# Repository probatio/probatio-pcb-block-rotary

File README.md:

# probatio-pcb-block-rotary
pcb for a probatio block of a rotary encoder with LEDs

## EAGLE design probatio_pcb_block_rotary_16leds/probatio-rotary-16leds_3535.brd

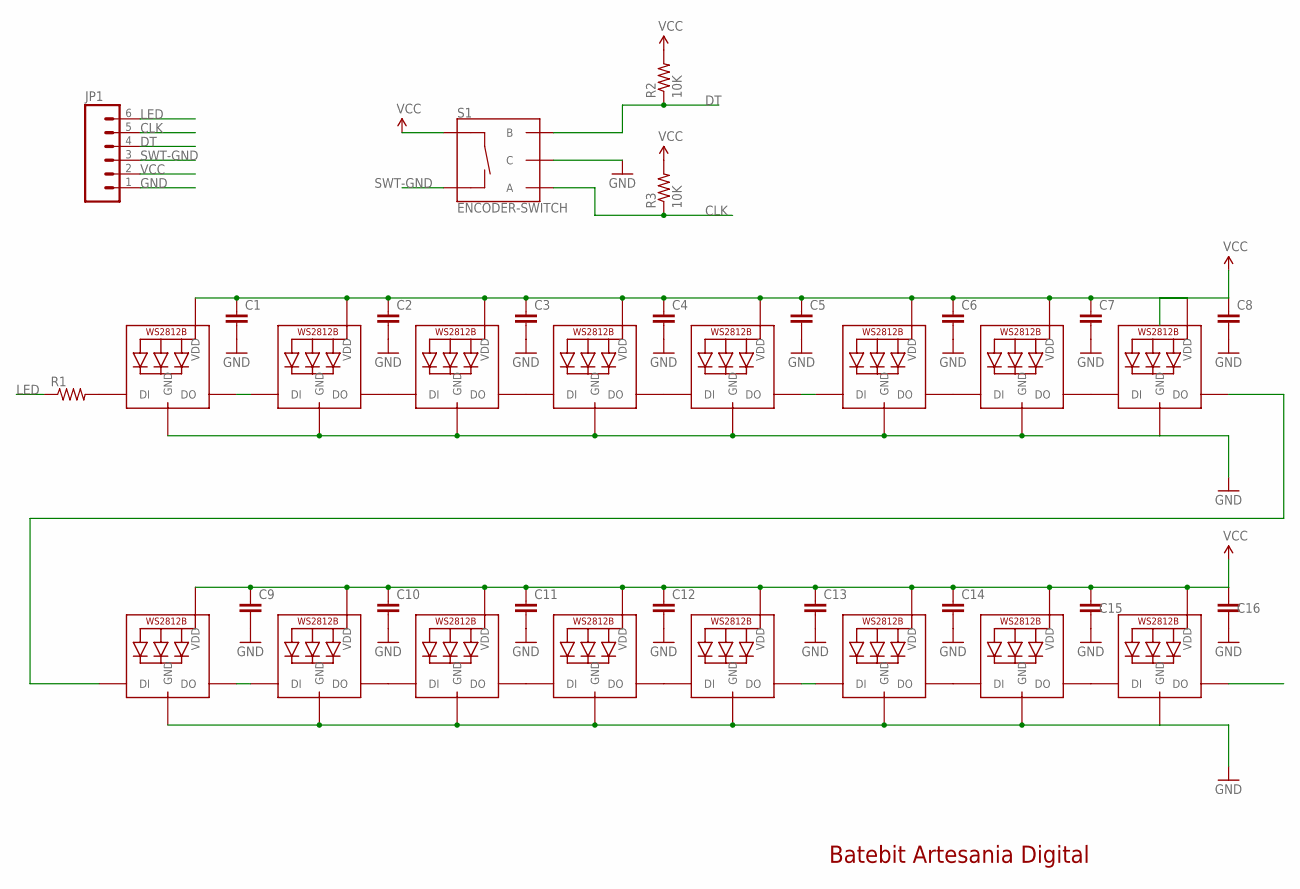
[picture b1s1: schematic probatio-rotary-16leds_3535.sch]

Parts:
C1, C2, C3, C4, C5, C6, C7, C8, C9, C10, C11, C12, C13, C14, C15, C16: CAP0805-CAP; 0805-CAP
JP1: M06SILK_FEMALE_PTH; 1X06
LED1, LED2, LED3, LED4, LED5, LED6, LED7, LED8, LED9, LED10, LED11, LED12, LED13, LED14, LED15, LED16: WS2812B3535; LED3535
R1: RESISTOR0805-RES; 0805-RES
R2, R3: 10K; 0805-RES
S1: ENCODER-SWITCH; ROTARY_ENC_PLAIN

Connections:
CLK: JP1.5, R3.1, S1.A
DT: JP1.4, R2.1, S1.B
GND: C1.2, C2.2, C3.2, C4.2, C5.2, C6.2, C7.2, C8.2, C9.2, C10.2, C11.2, C12.2, C13.2, C14.2, C15.2, C16.2, JP1.1, LED1.4 (GND), LED2.4 (GND), LED3.4 (GND), LED4.4 (GND), LED5.4 (GND), LED6.4 (GND), LED7.4 (GND), LED8.4 (GND), LED9.4 (GND), LED10.4 (GND), LED11.4 (GND), LED12.4 (GND), LED13.4 (GND), LED14.4 (GND), LED15.4 (GND), LED16.4 (GND), S1.C
LED: JP1.6, R1.1
unnamed: LED1.3 (DO), LED2.1 (DI)
unnamed: LED2.3 (DO), LED3.1 (DI)
unnamed: LED3.3 (DO), LED4.1 (DI)
unnamed: LED5.3 (DO), LED6.1 (DI)
unnamed: LED6.3 (DO), LED7.1 (DI)
unnamed: LED7.3 (DO), LED8.1 (DI)
unnamed: LED4.3 (DO), LED5.1 (DI)
unnamed: LED9.3 (DO), LED10.1 (DI)
unnamed: LED10.3 (DO), LED11.1 (DI)
unnamed: LED11.3 (DO), LED12.1 (DI)
unnamed: LED13.3 (DO), LED14.1 (DI)
unnamed: LED14.3 (DO), LED15.1 (DI)
unnamed: LED15.3 (DO), LED16.1 (DI)
unnamed: LED12.3 (DO), LED13.1 (DI)
unnamed: LED8.3 (DO), LED9.1 (DI)
unnamed: LED1.1 (DI), R1.2
SWT-GND: JP1.3, S1.SW-
VCC: C1.1, C2.1, C3.1, C4.1, C5.1, C6.1, C7.1, C8.1, C9.1, C10.1, C11.1, C12.1, C13.1, C14.1, C15.1, C16.1, JP1.2, LED1.2 (VDD), LED2.2 (VDD), LED3.2 (VDD), LED4.2 (VDD), LED5.2 (VDD), LED6.2 (VDD), LED7.2 (VDD), LED8.2 (VDD), LED9.2 (VDD), LED10.2 (VDD), LED11.2 (VDD), LED12.2 (VDD), LED13.2 (VDD), LED14.2 (VDD), LED15.2 (VDD), LED16.2 (VDD), R2.2, R3.2, S1.SW+

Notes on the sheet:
Batebit Artesania Digital

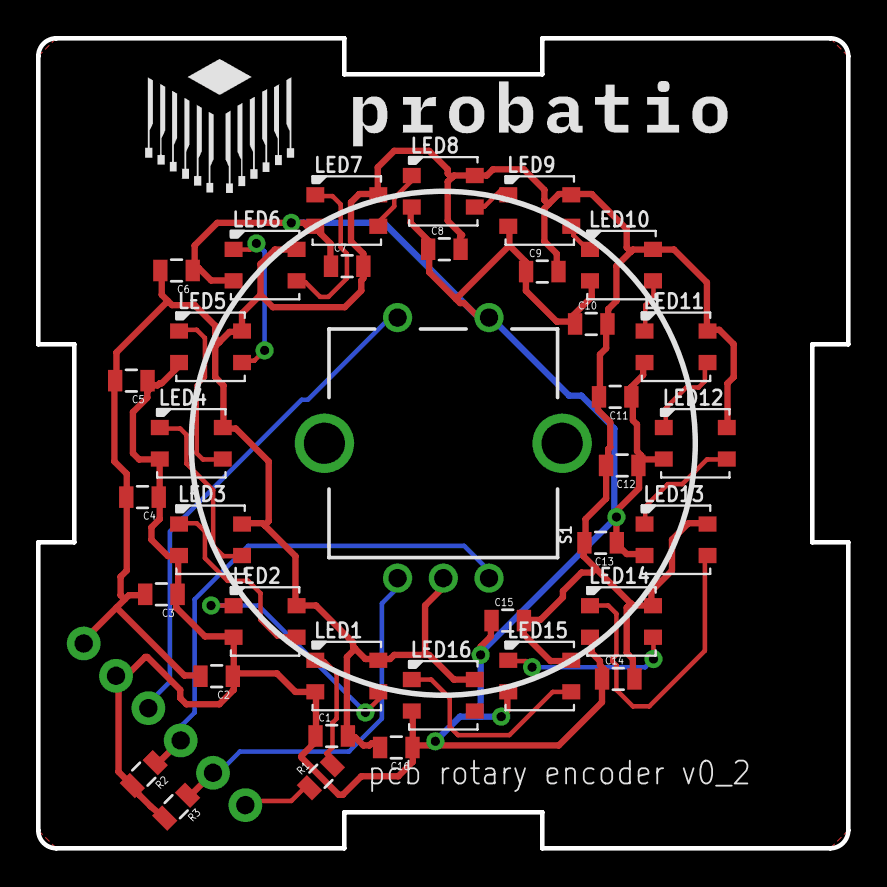
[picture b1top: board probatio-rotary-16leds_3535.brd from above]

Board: 2 copper layers, 45.0 x 45.0 mm, 38 parts (1 on the bottom side), 22 nets.

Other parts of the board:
U$3: PROBATIO

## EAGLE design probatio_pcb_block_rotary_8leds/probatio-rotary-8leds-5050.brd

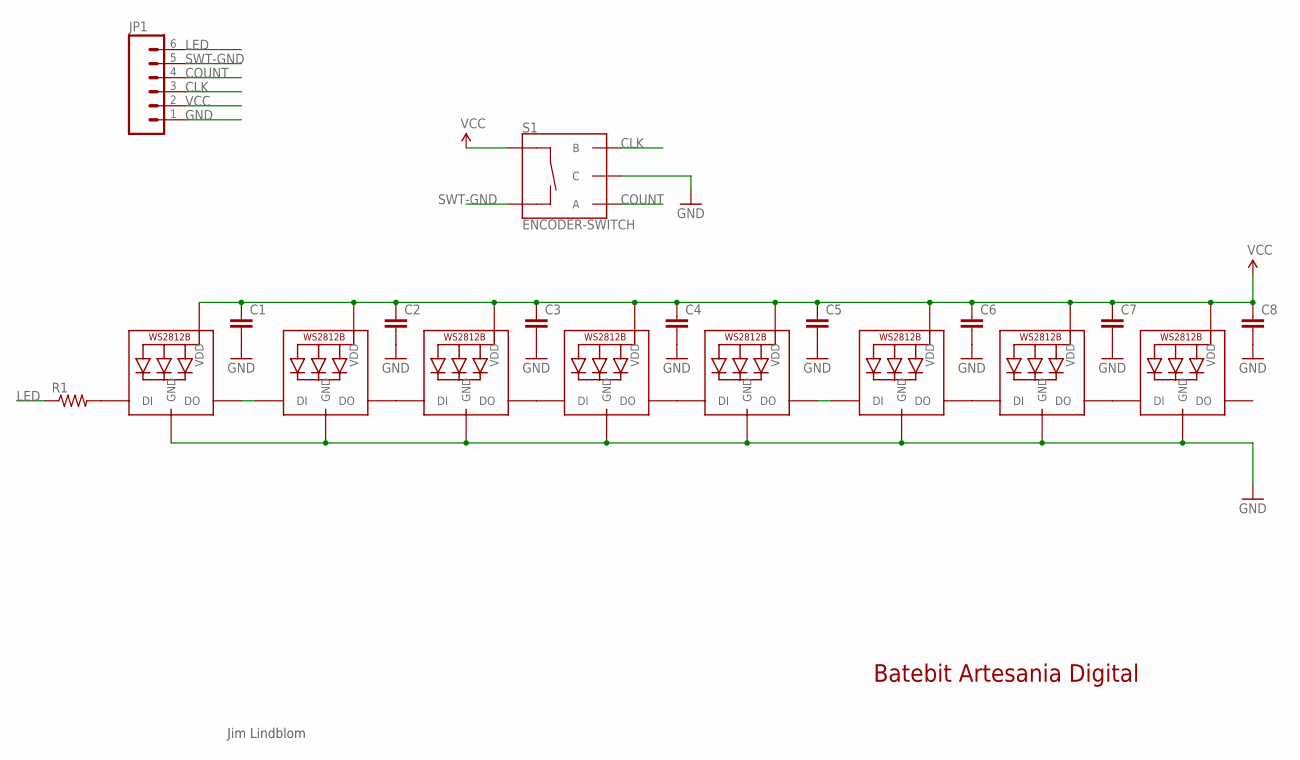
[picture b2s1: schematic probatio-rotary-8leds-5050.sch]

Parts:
C1, C2, C3, C4, C5, C6, C7, C8: CAP0805-CAP; 0805-CAP
JP1: M06SILK_FEMALE_PTH; 1X06
LED1, LED2, LED3, LED4, LED5, LED6, LED7, LED8: WS2812B5050; WS2812B
R1: RESISTOR0805-RES; 0805-RES
S1: ENCODER-SWITCH; ROTARY_ENC_PLAIN

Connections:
CLK: JP1.3, S1.B
COUNT: JP1.4, S1.A
GND: C1.2, C2.2, C3.2, C4.2, C5.2, C6.2, C7.2, C8.2, JP1.1, LED1.3-GND (GND), LED2.3-GND (GND), LED3.3-GND (GND), LED4.3-GND (GND), LED5.3-GND (GND), LED6.3-GND (GND), LED7.3-GND (GND), LED8.3-GND (GND), S1.C
LED: JP1.6, R1.1
unnamed: LED1.2-DOUT (DO), LED2.4-DIN (DI)
unnamed: LED1.4-DIN (DI), R1.2
unnamed: LED2.2-DOUT (DO), LED3.4-DIN (DI)
unnamed: LED5.2-DOUT (DO), LED6.4-DIN (DI)
unnamed: LED3.2-DOUT (DO), LED4.4-DIN (DI)
unnamed: LED4.2-DOUT (DO), LED5.4-DIN (DI)
unnamed: LED6.2-DOUT (DO), LED7.4-DIN (DI)
unnamed: LED7.2-DOUT (DO), LED8.4-DIN (DI)
SWT-GND: JP1.5, S1.SW-
VCC: C1.1, C2.1, C3.1, C4.1, C5.1, C6.1, C7.1, C8.1, JP1.2, LED1.1-VDD (VDD), LED2.1-VDD (VDD), LED3.1-VDD (VDD), LED4.1-VDD (VDD), LED5.1-VDD (VDD), LED6.1-VDD (VDD), LED7.1-VDD (VDD), LED8.1-VDD (VDD), S1.SW+

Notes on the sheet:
Batebit Artesania Digital
Jim Lindblom

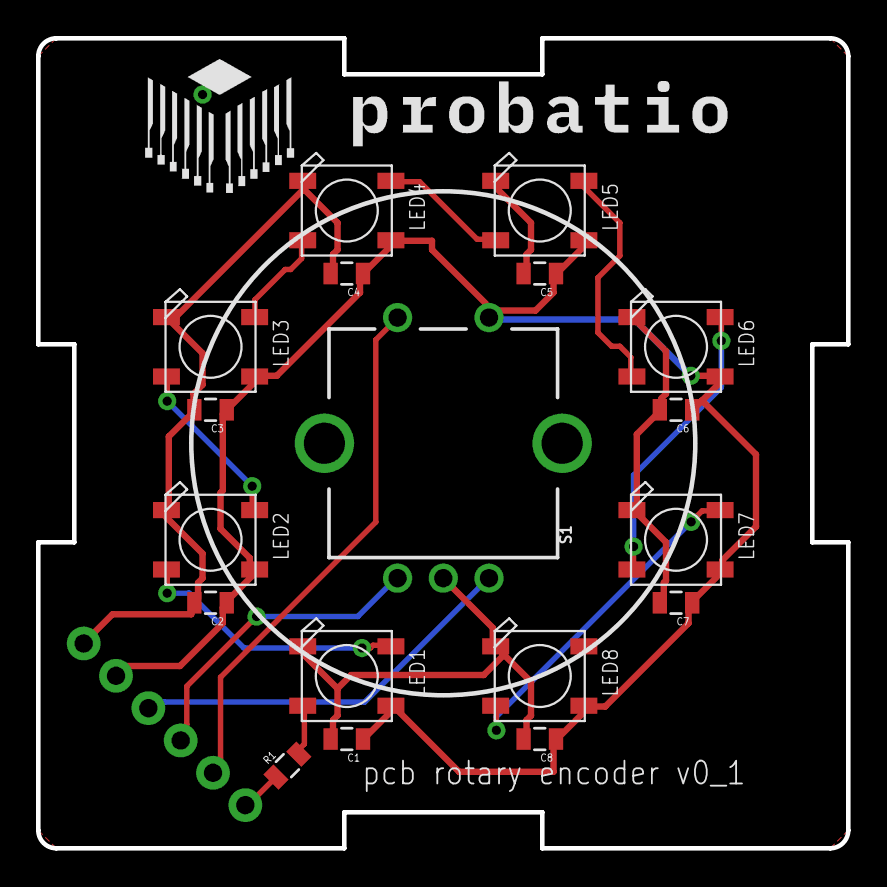
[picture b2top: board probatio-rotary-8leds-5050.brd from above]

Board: 2 copper layers, 45.0 x 45.0 mm, 20 parts (1 on the bottom side), 14 nets.

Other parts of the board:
U$3: PROBATIO

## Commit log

2021-02-25 16leds and 8leds versions
